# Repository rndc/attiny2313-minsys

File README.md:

attiny2313-minsys
=================

ATtiny2313 Minimal System

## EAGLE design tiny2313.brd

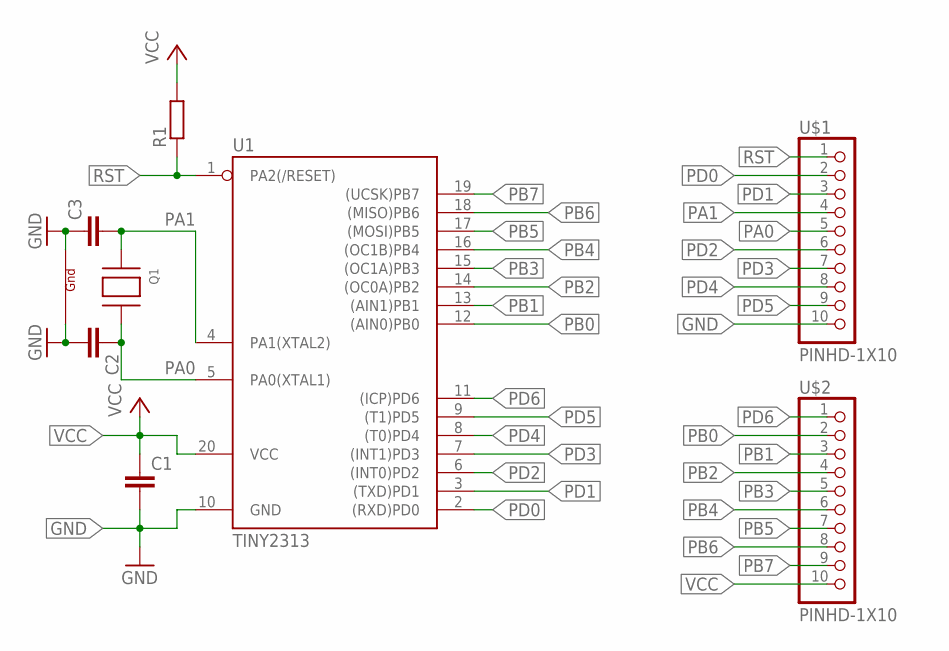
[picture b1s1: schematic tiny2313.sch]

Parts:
C1, C2, C3: C-EUC0805; C0805
Q1: XTAL-4-3225; NX3225
R1: R-EU_R0805; R0805
U1: TINY2313; SO20L$
U$1, U$2: PINHD-1X10; 1X10-BIG

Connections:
GND: C1.2, C2.2, C3.1, Q1.2 (G2), Q1.4 (G1), U1.10 (GND), U$1.10
PA0: C2.1, Q1.3 (X2), U1.5 (PA0(XTAL1)), U$1.5
PA1: C3.2, Q1.1 (X1), U1.4 (PA1(XTAL2)), U$1.4
PB0: U1.12 ((AIN0)PB0), U$2.2
PB1: U1.13 ((AIN1)PB1), U$2.3
PB2: U1.14 ((OC0A)PB2), U$2.4
PB3: U1.15 ((OC1A)PB3), U$2.5
PB4: U1.16 ((OC1B)PB4), U$2.6
PB5: U1.17 ((MOSI)PB5), U$2.7
PB6: U1.18 ((MISO)PB6), U$2.8
PB7: U1.19 ((UCSK)PB7), U$2.9
PD0: U1.2 ((RXD)PD0), U$1.2
PD1: U1.3 ((TXD)PD1), U$1.3
PD2: U1.6 ((INT0)PD2), U$1.6
PD3: U1.7 ((INT1)PD3), U$1.7
PD4: U1.8 ((T0)PD4), U$1.8
PD5: U1.9 ((T1)PD5), U$1.9
PD6: U1.11 ((ICP)PD6), U$2.1
RST: R1.1, U1.1 (PA2(/RESET)), U$1.1
VCC: C1.1, R1.2, U1.20 (VCC), U$2.10

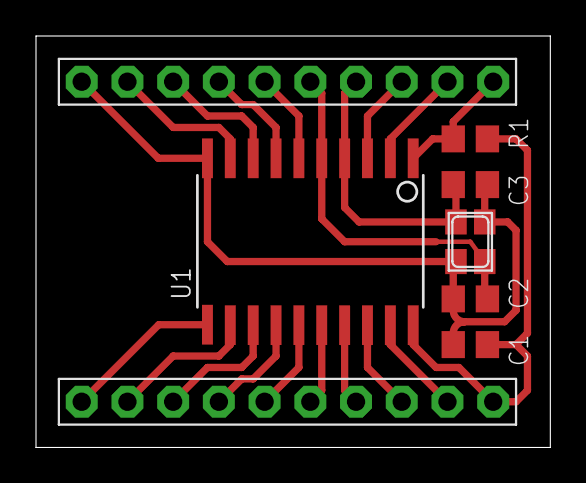
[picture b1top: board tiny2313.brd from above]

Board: 2 copper layers, 28.6 x 22.9 mm, 8 parts (0 on the bottom side), 20 nets.

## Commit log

2014-03-15 Added schematic and PCB files
